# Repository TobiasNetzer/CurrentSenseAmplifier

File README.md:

## High-Side current sense amplifier for precise current measurement (up to 100mA)
This high-side current sense amplifier is designed to enable accurate current measurement up to 100mA while maintaining a low burden voltage of 1mV/mA.
With a gain of 100, the amplifier produces an output voltage of 100mV/mA.

Documentation
- [Schematic](https://github.com/TobiasNetzer/CurrentSenseAmplifier/blob/main/Documentation/Schematic.pdf)
- [Assembly Drawing](https://github.com/TobiasNetzer/CurrentSenseAmplifier/blob/main/Documentation/Assembly%20Drawing.pdf)
- [BOM](https://htmlpreview.github.io/?https://github.com/TobiasNetzer/CurrentSenseAmplifier/blob/main/Documentation/BOM.html)

---

---

## Amplifier Accuracy

To test the accuracy of the current sense amplifier, various load currents are applied, and the amplifier’s output is compared to the corresponding load currents. The measurement error is then calculated and plotted as the deviation in percent from the actual value.

Across the tested current range form 5mA - 100mA, the error remained within ±0.2%.

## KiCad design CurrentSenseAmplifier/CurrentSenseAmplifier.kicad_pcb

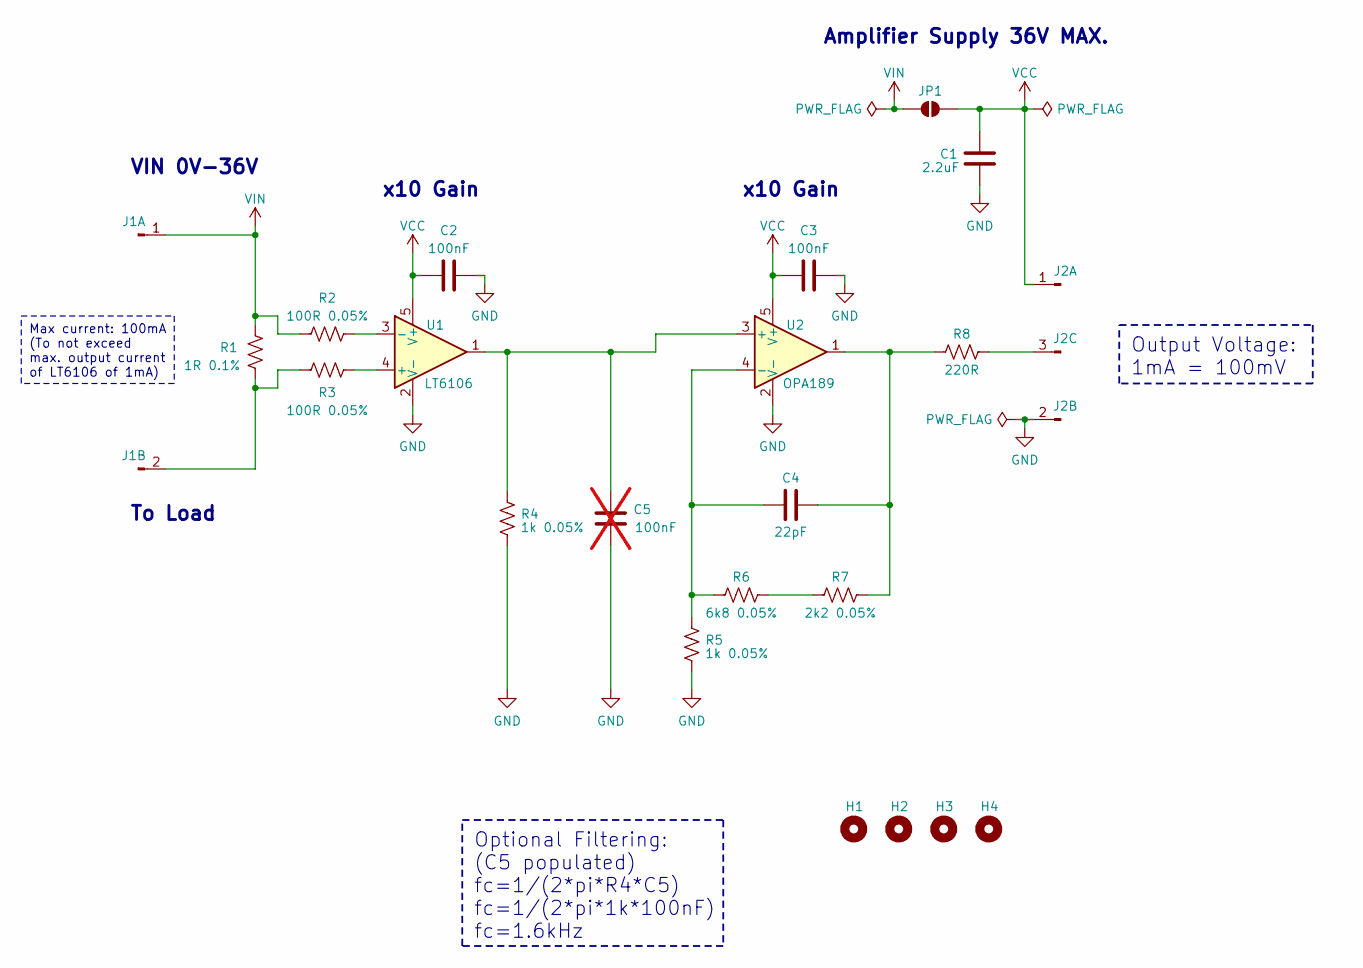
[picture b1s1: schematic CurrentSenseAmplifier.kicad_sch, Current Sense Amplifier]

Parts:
C1: 2.2uF; C_1206_(3216_Metric); Manufacturer Part Number C1206C225K5RACTU
C2, C3: 100nF; C_0402_(1005_Metric); Manufacturer Part Number C0402C104M3RACTU
C4: 22pF; C_0402_(1005_Metric); Manufacturer Part Number C0402C220J5GACTU
C5: 100nF; C_0402_(1005_Metric); Manufacturer Part Number C0402C104M3RACTU; not fitted
H1, H2, H3, H4: MountingHole; MountingHole_M2
J1: Header_1x03_P2.54; PinHeader_1x02_P2.54mm_Vertical; Manufacturer Part Number TSW-102-08-F-S
J2: Header_1x03_P2.54; PinHeader_1x03_P2.54mm_Vertical; Manufacturer Part Number TSW-103-08-F-S
JP1: SolderJumper_2; SolderJumper-2
R1: 1R 0.1%; R_1206_(3216_Metric); Manufacturer Part Number CPF1206B1R0E1
R2, R3: 100R 0.05%; R_0402_(1005_Metric); Manufacturer Part Number RG1005N-101-W-T5
R4, R5: 1k 0.05%; R_0402_(1005_Metric); Manufacturer Part Number RG1005V-102-W-T1
R6: 6k8 0.05%; R_0402_(1005_Metric); Manufacturer Part Number ERA-2VRW6801X
R7: 2k2 0.05%; R_0402_(1005_Metric); Manufacturer Part Number ERA-2VRW2201X
R8: 220R; R_0402_(1005_Metric); Manufacturer Part Number RC0402FR-13220RL
U1: LT6106; SOT-23-5; Manufacturer Part Number LT6106IS5#TRMPBF
U2: OPA189; SOT-23-5; Manufacturer Part Number OPA189IDBVR

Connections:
GND: C1.2, C2.2, C3.2, C5.2, J2.2, R4.1, R5.1, U1.2 (V-), U2.2 (V-)
unnamed: C4.2, R7.2, R8.1, U2.1
unnamed: J1.2, R1.2, R3.1
unnamed: J2.3, R8.2
unnamed: R6.2, R7.1
unnamed: R3.2, U1.4 (+)
unnamed: R2.2, U1.3 (-)
unnamed: C5.1, R4.2, U1.1, U2.3 (+)
unnamed: C4.1, R5.2, R6.1, U2.4 (-)
VCC: C1.1, C2.1, C3.1, J2.1, JP1.2 (B), U1.5 (V+), U2.5 (V+)
VIN: J1.1, JP1.1 (A), R1.1, R2.1

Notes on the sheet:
Output Voltage: 1mA = 100mV
Optional Filtering: (C5 populated) fc=1/(2*pi*R4*C5) fc=1/(2*pi*1k*100nF) fc=1.6kHz
Max current: 100mA (To not exceed max. output current of LT6106 of 1mA)
x10 Gain
VIN 0V-36V
To Load
Amplifier Supply 36V MAX.

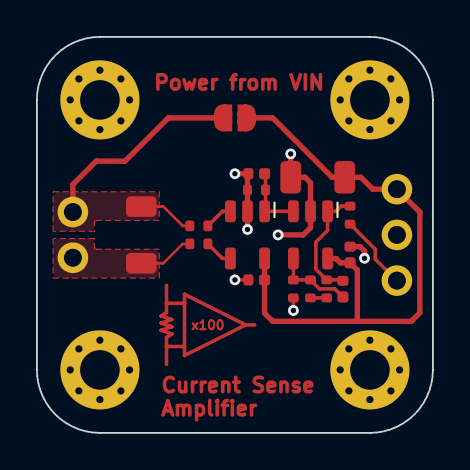
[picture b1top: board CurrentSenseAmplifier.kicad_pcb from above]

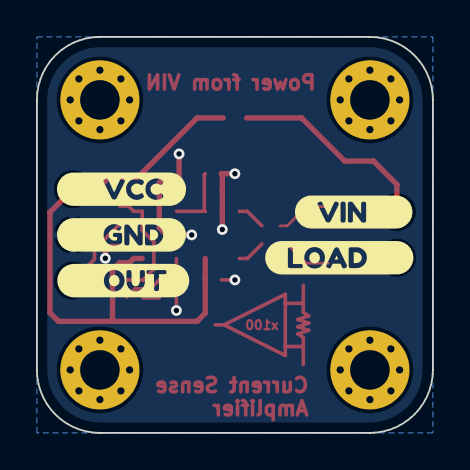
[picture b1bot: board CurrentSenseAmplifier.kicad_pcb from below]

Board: 2 copper layers, 22.0 x 22.0 mm, 27 parts (5 on the bottom side), 11 nets.

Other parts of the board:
kibuzzard-64025D5B: G***; kibuzzard-64025D5B
kibuzzard-64025D53: G***; kibuzzard-64025D53
kibuzzard-64025D67: G***; kibuzzard-64025D67
kibuzzard-64027212: G***; kibuzzard-64027212
kibuzzard-64027225: G***; kibuzzard-64027225

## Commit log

2025-04-24 add accuracy diagram
2025-04-24 add render
